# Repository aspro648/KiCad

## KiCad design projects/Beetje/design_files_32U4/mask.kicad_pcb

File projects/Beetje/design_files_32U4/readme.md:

Beetje Blok 32U4

Based on Adafruit's [ItsyBitsy](https://learn.adafruit.com/introducting-itsy-bitsy-32u4) and SparkFun's [Pro Micro](https://www.sparkfun.com/products/12587) 3.3V/8Mhz versions.

Project page on [Hack-A-Day](https://hackaday.io/project/160638-beetje-bloks).

This is the first "dev blok" for this proof-of-concept project.  It is a KiCad mash-up of Adafruit's [ItsyBity](https://learn.adafruit.com/introducting-itsy-bitsy-32u4) and SparkFun's [Pro Micro](https://www.sparkfun.com/products/12587), jammed into Hack-A-Day's [Once Square Inch Scheme](https://hackaday.io/project/7813-the-square-inch-project) ("HADOSIS").

Bill Of Materials
----------------
  
- 1 ea., Perfect Purple PCB from OSH Park, with not so perfect kicad.pcb file.
- 1 ea., U1, ATMEGA32U4-AU, IC MCU 8BIT 32KB FLASH 44TQFP, https://www.digikey.com/short/jb25pc
- 1 ea., U2, IC REG LINEAR 3.3V 150MA SOT23-5, MIC5225-3.3YM5-TR, https://www.digikey.com/short/jb2rq8
- 3 ea,, C1-C3 10uF SMD 0805, https://www.digikey.com/short/j5d39w 
- 1 ea., C4 1uF SMD 0603, https://www.digikey.com/short/j5d397
- 3 ea., D1-D3 0603 SMD LED, https://www.digikey.com/short/j5h3h5
- 2 ea., D4, D5 DIODE SCHOTTKY 20V 1A SOD123FL, MBR120ESFT1G, https://www.digikey.com/short/jnqvz9
- 1 ea., F1 PTC 1206, Bel 0ZCJ0025AF2E, https://www.digikey.com/short/jfcbc8
- 3 ea., R1-R3 1K Ohm 0603 SMD resistor, https://www.digikey.com/short/jfcb32
- 2 ea., R4, R5 Resistor 4.7K SMD 0603, https://www.digikey.com/short/j2d05w
- 2 ea., R6, R7, 22 Ohm 5% 0603 SMD resistor, https://www.digikey.com/short/jfcbtj
- 1 ea., R8 100K ohm 0603 SMD resistor, https://www.digikey.com/short/jnqvjq
- 2 ea., SW1, Sw2 RA Tactile SPST, Pansonic EVQ-P7J01P, https://www.digikey.com/short/jfwprn
- 1 ea., X1 CONN RCPT MICRO USB R/A SMD, Molex 1050170001, https://www.digikey.com/short/jb2205
- 1 ea., Y1 Resonator 8MHZ, CSTNE8M00G55Z000R0, https://www.digikey.com/short/jb22j1

Headers:
--------

- J2, CONN HEADER FEMALE 6POS .1" GOLD, https://www.digikey.com/short/jfcnz3
- J4, CONN HEADER FEMALE 8POS .1" GOLD, https://www.digikey.com/short/jfcnzj
   or
- Stacking Arduino headers like https://www.digikey.com/short/jfcnz3
   or
- 1 ea., 64-pin header(enough for 4.5 boards) Mill-max 311-43-164-41-001000, https://www.digikey.com/short/jnqdm2
   or
- 1 ea., CONN SOCKET SIP 8POS GOLD, Mill-Max 315-47-108-41-001000, https://www.digikey.com/short/jn51q5
- 1 ea., CONN SOCKET SIP 6POS GOLD, Mill-Max 315-47-106-41-001000, https://www.digikey.com/short/jn5188

Revisions
----------------
- Revision 0.1 - Diodes and polyfuse to front.
- Revision 0.2 - I2C pullups, added SW2, enlarge holes for headers.
- Revision 0.3 - Pinout change, rerouted. NOT BACKWARD COMPATIBLE.
- Revision 0.4 - Renumbering, reordering references.

License
----------------
[Attribution-ShareAlike 3.0 United States (CC BY-SA 3.0 US)](https://creativecommons.org/licenses/by-sa/3.0/us/)

You are free to:

- Share — copy and redistribute the material in any medium or format
- Adapt — remix, transform, and build upon the material

Under the following terms:

- Attribution — You must give appropriate credit, provide a link to the license, and indicate if changes were made. You may do so in any reasonable manner, but not in any way that suggests the licensor endorses you or your use.
- ShareAlike — If you remix, transform, or build upon the material, you must distribute your contributions under the same license as the original.

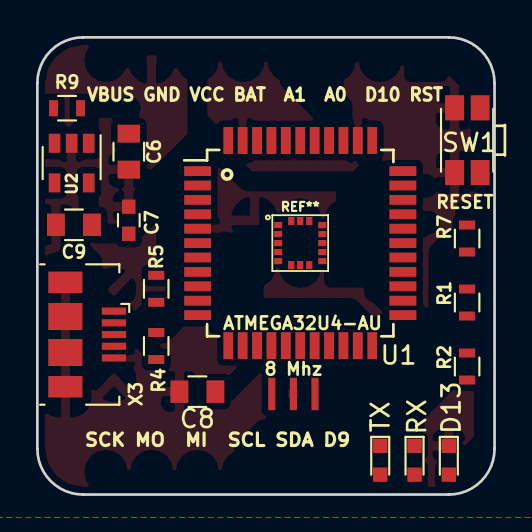
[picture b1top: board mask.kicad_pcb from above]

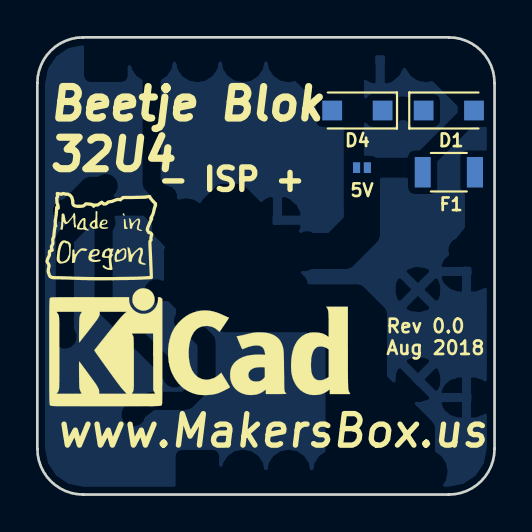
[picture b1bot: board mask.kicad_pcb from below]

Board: 2 copper layers, 25.4 x 25.4 mm, 23 parts (4 on the bottom side), 19 nets, no tracks yet.

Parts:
C6, C8, C9: 10uF; C_0805
C7: 1uF; C_0603
D1, D4: MBR120; D_SOD-123F
D3: TX; LED_0603
D5: RX; LED_0603
D13: D13; LED_0603
F1: Polyfuse; R_1206
JMP1: 5V; Jumper
R1, R2, R7: 180; R_0603
R4, R5: 22; R_0603
R9: 100K; R_0603
SW1: RESET; EVQ-P7A
U1: ATMEGA32U4-AU; TQFP-44_10x10mm_Pitch0.8mm
U2: MIC5225-3.3; SOT-23-5
VAL: MadeInOregonRev25
X3: USB_OTG; USB_Micro-B_Molex-105017-0001
Y1: 8 Mhz; Resonator_SMD_CTSC_1.3mmx3.2mm

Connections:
/D13: R7.2, U1.32
/D+: R4.1, U1.4
/D-: R5.1, U1.3
/RXLED: R2.1, U1.8
/TXLED: R1.1, U1.22
/VHI: C6.1, D1.1, D4.1, R9.2, U2.1
/~RESET: SW1.2, U1.13
GND: C6.2, C7.2, C8.2, C9.2, D13.1, SW1.1, U1.5, U1.15, U1.23, U1.35, U1.43, U2.2, X3.5, X3.6, Y1.2
unnamed: D3.1, R1.2
unnamed: D5.1, R2.2
unnamed: D13.2, R7.1
unnamed: F1.2, X3.1
unnamed: R4.2, X3.3
unnamed: R5.2, X3.2
unnamed: R9.1, U2.3
unnamed: U1.16, Y1.3
unnamed: U1.17, Y1.1
VBUS: D1.2, F1.1, JMP1.2, U1.7
VCC: C7.1, C8.1, C9.1, D3.2, D5.2, JMP1.1, U1.6, U1.14, U1.24, U1.33, U1.34, U1.44, U2.5

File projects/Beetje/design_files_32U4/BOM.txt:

Beetje Blok 32U4 Rev 0.0

Bill Of Materials
----------------
  
- 1 ea., Perfect Purple PCB from OSH Park, with not so perfect layout from [design_files](design_files/) folder.
- U1, ATMEGA32U4-AU, IC MCU 8BIT 32KB FLASH 44TQFP, https://www.digikey.com/short/jb25pc
- U2, IC REG LINEAR 3.3V 150MA SOT23-5, MIC5225-3.3YM5-TR, https://www.digikey.com/short/jb2rq8
- Y1, Resonator 8MHZ, CSTNE8M00G55Z000R0, https://www.digikey.com/short/jb22j1
- D1, D4, DIODE SCHOTTKY 20V 1A SOD123FL, MBR120VLSFT3GOSCT-ND, https://www.digikey.com/short/jb22rn 
- C6, C8, C9, 10uF SMD 0805, https://www.digikey.com/short/j5d39w 
- C7 1uF SMD 0603, https://www.digikey.com/short/j5d397
- X3, CONN RCPT MICRO USB R/A SMD, Molex 1050170001, https://www.digikey.com/short/jb2205
- R4, R5, 22 Ohm 5% 0603 SMD resistor, https://www.digikey.com/short/jfcbtj
- R1, R2, R7, 330 Ohm 0603 SMD resistor, https://www.digikey.com/short/jfcb32
- R9, 100K ohm 0603 SMD resistor, https://www.digikey.com/short/j5d3b3
- D3, D5, D13, 0603 SMD LED, https://www.digikey.com/short/j5h3h5
- F1, PTC 1206, Bel 0ZCJ0025AF2E, https://www.digikey.com/short/jfcbc8
- SW1, RA Tactile SPST, Pansonic EVQ-PA01P, https://www.digikey.com/short/jfc9vq
- J2, CONN HEADER FEMALE 6POS .1" GOLD, https://www.digikey.com/short/jfcnz3
- J4, CONN HEADER FEMALE 8POS .1" GOLD, https://www.digikey.com/short/jfcnzj

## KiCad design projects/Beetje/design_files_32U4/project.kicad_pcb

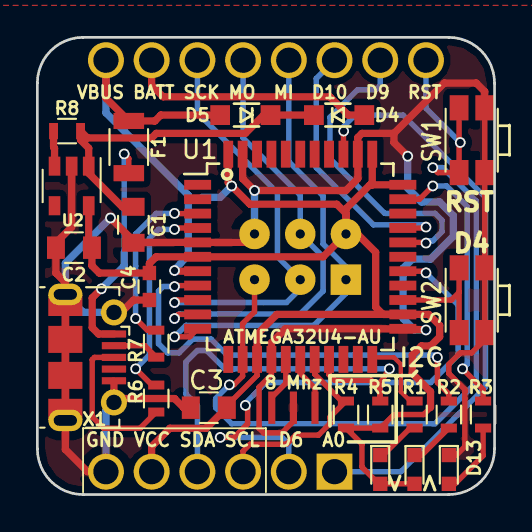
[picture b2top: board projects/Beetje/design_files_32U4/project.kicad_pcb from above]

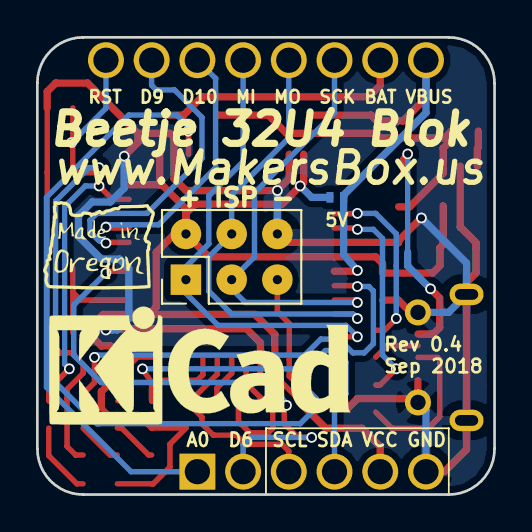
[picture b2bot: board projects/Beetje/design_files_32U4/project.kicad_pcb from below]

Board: 2 copper layers, 25.4 x 25.4 mm, 29 parts (2 on the bottom side), 30 nets.

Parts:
C1, C2, C3: 10uF; C_0805
C4: 1uF; C_0603
CON1: AVR-ISP-6; Pin_Header_Straight_2x03_Pitch2.54mm
D1: TX; LED_0603
D2: RX; LED_0603
D3: D13; LED_0603
D4, D5: MBR120; D_SOD-123F
F1: Polyfuse; R_1206
J2: Beetje Bottom; Beetje_Bottom
J4: Beetje Top; Beetje_Top
JMP1: 5V; Jumper
R1, R2, R3: 1K; R_0603
R4, R5: 4K7; R_0603
R6, R7: 22; R_0603
R8: 100K; R_0603
SW1: RST; EVQ-P7A
SW2: D4; EVQ-P7A
U1: ATMEGA32U4-AU; TQFP-44_10x10mm_Pitch0.8mm
U2: MIC5225-3.3; SOT-23-5
VAL: MadeInOregonRev25
X1: USB_OTG; USB_Micro-B_Molex-105017-0001
Y1: 8 Mhz; Resonator_SMD_CTSC_1.3mmx3.2mm

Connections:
+BATT: D4.2, J4.7
/A0: J2.1, U1.36
/D4: SW2.1, U1.25
/D6: J2.2, U1.27
/D9: J4.2, U1.29
/D10: J4.3, U1.30
/D13: R3.2, U1.32
/D+: R6.1, U1.4
/D-: R7.1, U1.3
/MISO: CON1.1, J4.4, U1.11
/MOSI: CON1.4, J4.5, U1.10
/RXLED: R2.1, U1.8
/SCK: CON1.3, J4.6, U1.9
/SCL: J2.3, R4.1, U1.18
/SDA: J2.4, R5.1, U1.19
/TXLED: R1.1, U1.22
/VHI: C1.1, D4.1, D5.1, R8.2, U2.1
/~RESET: CON1.5, J4.1, SW1.1, U1.13
GND: C1.2, C2.2, C3.2, C4.2, CON1.6, D3.1, J2.6, SW1.2, SW2.2, U1.5, U1.15, U1.23, U1.35, U1.43, U2.2, X1.5, X1.6, Y1.2
unnamed: D1.1, R1.2
unnamed: D2.1, R2.2
unnamed: D3.2, R3.1
unnamed: F1.2, X1.1
unnamed: R6.2, X1.3
unnamed: R7.2, X1.2
unnamed: R8.1, U2.3
unnamed: U1.16, Y1.3
unnamed: U1.17, Y1.1
VBUS: D5.2, F1.1, J4.8, JMP1.2, U1.7
VCC: C2.1, C3.1, C4.1, CON1.2, D1.2, D2.2, J2.5, JMP1.1, R4.2, R5.2, U1.6, U1.14, U1.24, U1.33, U1.34, U1.44, U2.5

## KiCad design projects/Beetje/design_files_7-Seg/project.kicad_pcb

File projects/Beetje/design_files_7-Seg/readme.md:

Beetje Blok 7-SEG Rev 0.0

Project website: https://hackaday.io/project/160638-beetje-bloks

Based on Adafruit's [LED Backpack]{https://learn.adafruit.com/adafruit-led-backpack/downloads}. 

Bill Of Materials
----------------
  
- 1 ea., Perfect Purple PCB from OSH Park, with not so perfect layout from [design_files](design_files/) folder.
- 1 ea., IC1 Holtek HT16K33, https://lcsc.com/product-detail/LED-Drivers_HT16K33_C87502.html
- 1 ea., U1 7-segment CC LED
- 1 ea., C1 CAP CER 10UF 50V X7R, https://www.digikey.com/short/j5d39w 
- 1 ea., D1 DIODE SCHOTTKY 20V 1A SOD123L, https://www.digikey.com/short/j2wzf5
- 2 ea., R1, R2 Resistor 10K 0805 SMD, https://www.digikey.com/short/j2d0w4
- 3 ea., R3, R4, R5 Resistor 47K 0805 SMD, https://www.digikey.com/short/j2d00m 
- 1 ea., CONN HEADER .100" SNGL STR 40POS, https://www.digikey.com/short/jfcn42
- 1 ea., SW1 RA Tactile SPST, Pansonic EVQ-P7J01P, https://www.digikey.com/short/jfwprn

try https://lcsc.com/product-detail/Led-Segment-Display_0-28-Digitron-red-RED_C109199.html

License
----------------
[Attribution-ShareAlike 3.0 United States (CC BY-SA 3.0 US)](https://creativecommons.org/licenses/by-sa/3.0/us/)

You are free to:

- Share — copy and redistribute the material in any medium or format
- Adapt — remix, transform, and build upon the material

Under the following terms:

- Attribution — You must give appropriate credit, provide a link to the license, and indicate if changes were made. You may do so in any reasonable manner, but not in any way that suggests the licensor endorses you or your use.
- ShareAlike — If you remix, transform, or build upon the material, you must distribute your contributions under the same license as the original.

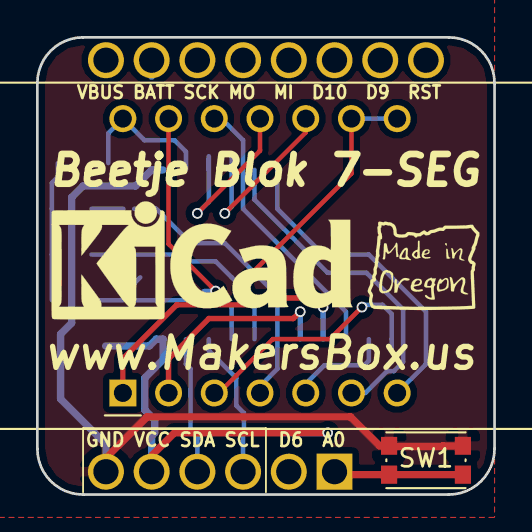
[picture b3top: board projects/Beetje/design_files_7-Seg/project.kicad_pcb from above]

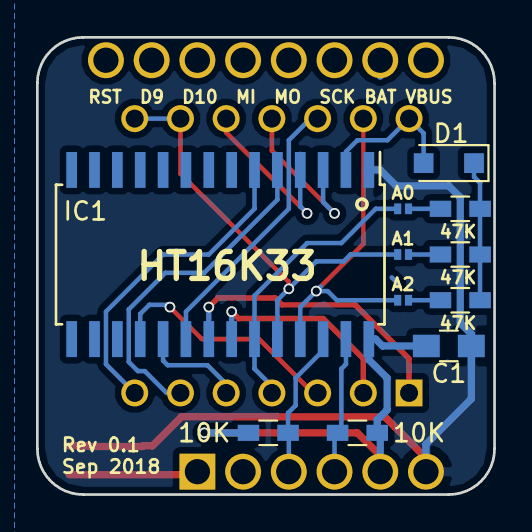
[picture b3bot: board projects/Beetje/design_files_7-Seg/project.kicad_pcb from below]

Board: 2 copper layers, 25.4 x 25.4 mm, 16 parts (12 on the bottom side), 22 nets.

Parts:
A0, A1, A2: JMP; Jumper
C1: 10uF; C_0805_HandSoldering
D1: D; D_SOD-123F
IC1: HT16K33; SOIC-28W_7.5x17.9mm_Pitch1.27mm
J2: Beetje_Bottom
J4: Beetje_Top
R1, R2: 10K; R_0603_HandSoldering
R3, R4, R5: 47K; R_0603_HandSoldering
SW1: SW_Push; SW_SPST_KMR2
U3: KW4-56xxx; CA56-12CGKWA
VAL: MadeInOregonRev25

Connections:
/A0: A0.2, IC1.23, U3.4
/A1: A1.2, IC1.24, U3.8, U3.9
/A2: A2.2, IC1.25, U3.13
/An0: J2.1, SW1.1
/SCL: IC1.26, J2.3, R2.1
/SDA: IC1.27, J2.4, R1.1
GND: C1.2, IC1.1, J2.6, SW1.2
unnamed: A0.1, R3.1
unnamed: A1.1, R4.1
unnamed: A2.1, R5.1
unnamed: D1.1, R3.2, R4.2, R5.2
unnamed: D1.2, IC1.2, U3.14
unnamed: IC1.3, U3.11
unnamed: IC1.4, U3.10
unnamed: IC1.5, U3.6
unnamed: IC1.6, U3.7
unnamed: IC1.18, U3.3
unnamed: IC1.19, U3.5
unnamed: IC1.20, U3.12
unnamed: IC1.21, U3.1
unnamed: IC1.22, U3.2
VCC: C1.1, IC1.28, J2.5, R1.2, R2.2

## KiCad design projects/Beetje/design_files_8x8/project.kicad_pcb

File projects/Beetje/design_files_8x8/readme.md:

Beetje Blok 7-SEG Rev 0.0

Project website: https://hackaday.io/project/160638-beetje-bloks

Based on Adafruit's [LED Backpack]{https://learn.adafruit.com/adafruit-led-backpack/downloads}. 

Bill Of Materials
----------------
  
- 1 ea., Perfect Purple PCB from OSH Park, with not so perfect layout from [design_files](design_files/) folder.
- 1 ea., IC1 Holtek HT16K33
- 1 ea., U1 7-segment CC LED
- 1 ea., C1 CAP CER 10UF 50V X7R, https://www.digikey.com/short/j5d39w 
- 2 ea., R1, R2 Resistor 10K 0805 SMD, https://www.digikey.com/short/j2d0w4
- 3 ea., R3, R4, R5 Resistor 47K 0805 SMD, https://www.digikey.com/short/j2d00m 
- 1 ea., CONN HEADER .100" SNGL STR 40POS, https://www.digikey.com/short/jfcn42
- 1 ea., SW1 RA Tactile SPST, Pansonic EVQ-P7J01P, https://www.digikey.com/short/jfwprn

License
----------------
[Attribution-ShareAlike 3.0 United States (CC BY-SA 3.0 US)](https://creativecommons.org/licenses/by-sa/3.0/us/)

You are free to:

- Share — copy and redistribute the material in any medium or format
- Adapt — remix, transform, and build upon the material

Under the following terms:

- Attribution — You must give appropriate credit, provide a link to the license, and indicate if changes were made. You may do so in any reasonable manner, but not in any way that suggests the licensor endorses you or your use.
- ShareAlike — If you remix, transform, or build upon the material, you must distribute your contributions under the same license as the original.

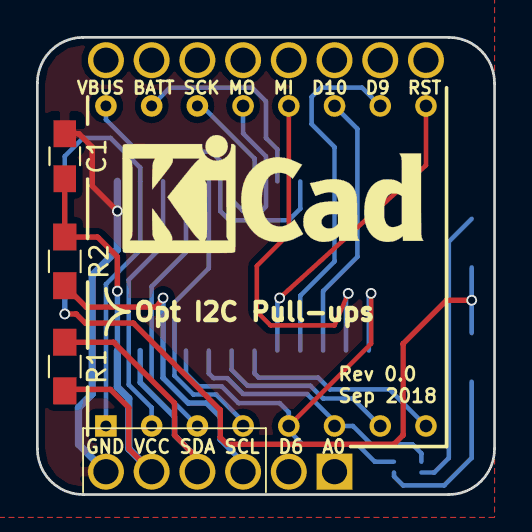
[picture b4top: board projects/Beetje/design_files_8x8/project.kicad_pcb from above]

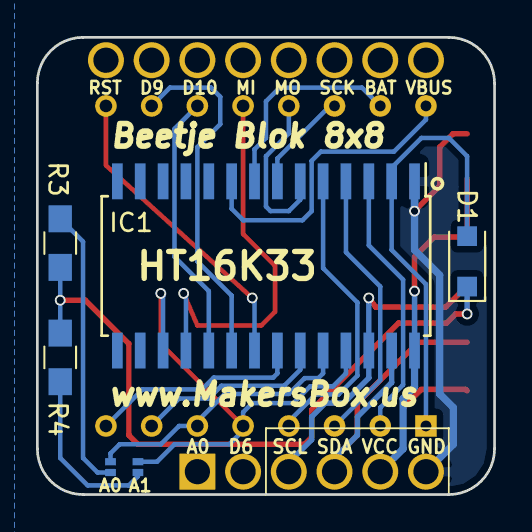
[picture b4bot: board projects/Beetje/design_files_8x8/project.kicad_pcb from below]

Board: 2 copper layers, 25.4 x 25.4 mm, 13 parts (6 on the bottom side), 23 nets.

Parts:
A0, A1: JMP; Jumper
C1: 10uF; C_0805_HandSoldering
D1: D; D_SOD-123F
IC1: HT16K33; SOIC-28W_7.5x17.9mm_Pitch1.27mm
J1, J3: CONN_01X08; Pin_Header_Straight_1x08_Pitch2.54mm
J2: Beetje_Bottom
J4: Beetje_Top
R1, R2, R3, R4: 10K; R_0805_HandSoldering

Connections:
/P1: D1.2, IC1.2, J3.1
/P2: IC1.3, J3.2
/P3: IC1.4, J3.3
/P4: IC1.5, J3.4
/P5: A1.2, IC1.17, IC1.25, J3.5
/P6: A0.2, IC1.24, J3.6
/P7: IC1.23, J3.7
/P8: IC1.22, J3.8
/P9: IC1.9, J1.1
/P10: IC1.8, J1.2
/P11: IC1.7, J1.3
/P12: IC1.6, J1.4
/P13: IC1.18, J1.5
/P14: IC1.19, J1.6
/P15: IC1.20, J1.7
/P16: IC1.21, J1.8
/SCL: IC1.26, J2.3, R2.1
/SDA: IC1.27, J2.4, R1.1
GND: C1.2, IC1.1, J2.6
unnamed: A0.1, R3.1
unnamed: A1.1, R4.1
unnamed: D1.1, R3.2, R4.2
VCC: C1.1, IC1.28, J2.5, R1.2, R2.2

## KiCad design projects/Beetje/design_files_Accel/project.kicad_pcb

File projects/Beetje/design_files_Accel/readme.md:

Beetje Blok Accel

Project website: https://hackaday.io/project/160638-beetje-bloks

Bill Of Materials
----------------
  
- 1 ea., Perfect Purple PCB from OSH Park, with not so perfect layout from [project.kicad_pcb](project.kicad_pcb) file.
- 1 ea., U1 ACCEL 2-16G I2C/SPI 16LGA, STM LIS331DLHTR, https://www.digikey.com/short/zzdzr7
- 1 ea., C1 10uF CAP SMD 0805, https://www.digikey.com/short/jnwj88
- 1 ea., C2 0.1uF CAP SMD 0805, https://www.digikey.com/short/j58qjp
- 1 ea., R1 10K OHM SMD 0805, https://www.digikey.com/short/j2d0w4 
- 2 ea., R2, R3 4K7 OHM SMD 0805, https://www.digikey.com/short/j2d0wd

Revisions
------------------

0.1 Pinout to Rev 0.3, 0805 Footprints

License
----------------
[Attribution-ShareAlike 3.0 United States (CC BY-SA 3.0 US)](https://creativecommons.org/licenses/by-sa/3.0/us/)

You are free to:

- Share — copy and redistribute the material in any medium or format
- Adapt — remix, transform, and build upon the material

Under the following terms:

- Attribution — You must give appropriate credit, provide a link to the license, and indicate if changes were made. You may do so in any reasonable manner, but not in any way that suggests the licensor endorses you or your use.
- ShareAlike — If you remix, transform, or build upon the material, you must distribute your contributions under the same license as the original.

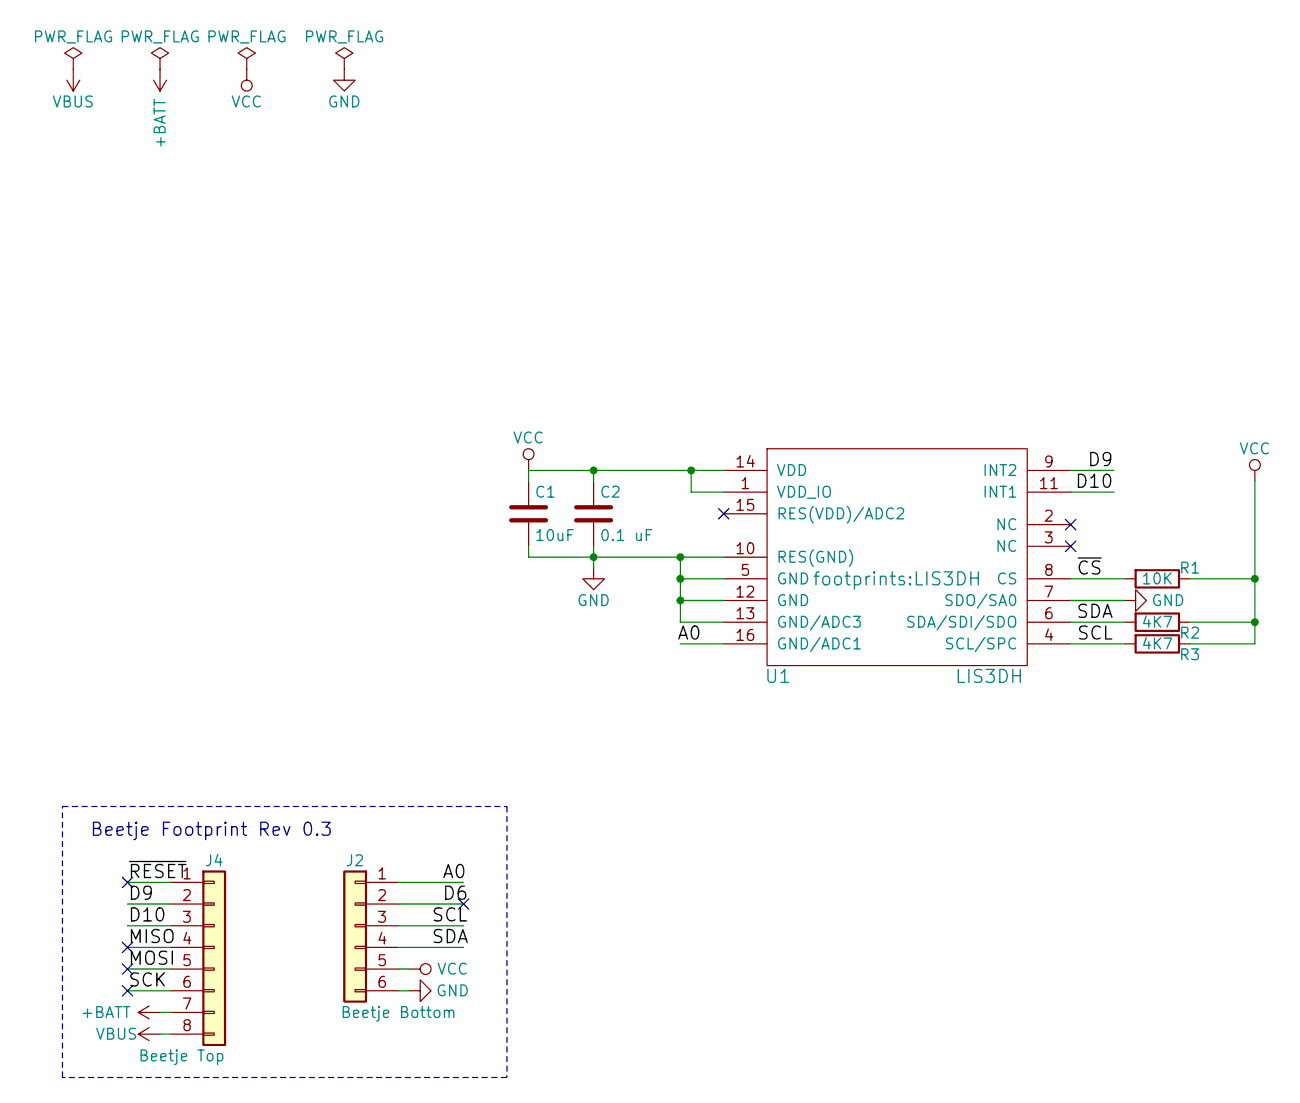
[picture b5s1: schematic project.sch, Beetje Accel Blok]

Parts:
C1: 10uF; C_0805
C2: 0.1 uF; C_0603
J2: Beetje Bottom; Beetje_Bottom
J4: Beetje Top; Beetje_Top
R1: 10K; R_0603
R2, R3: 4K7; R_0603
U1: LIS3DH

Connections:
+BATT: J4.7
/A0: J2.1, U1.16 (GND/ADC1)
/D6: J2.2
/D9: J4.2, U1.9 (INT2)
/D10: J4.3, U1.11 (INT1)
/MISO: J4.4
/MOSI: J4.5
/SCK: J4.6
/SCL: J2.3, R3.2, U1.4 (SCL/SPC)
/SDA: J2.4, R2.2, U1.6 (SDA/SDI/SDO)
/~CS: R1.2, U1.8 (CS)
/~RESET: J4.1
GND: C1.2, C2.2, J2.6, U1.5 (GND), U1.7 (SDO/SA0), U1.10 (RES(GND)), U1.12 (GND), U1.13 (GND/ADC3)
VBUS: J4.8
VCC: C1.1, C2.1, J2.5, R1.1, R2.1, R3.1, U1.1 (VDD_IO), U1.14 (VDD)

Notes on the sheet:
Beetje Footprint Rev 0.3

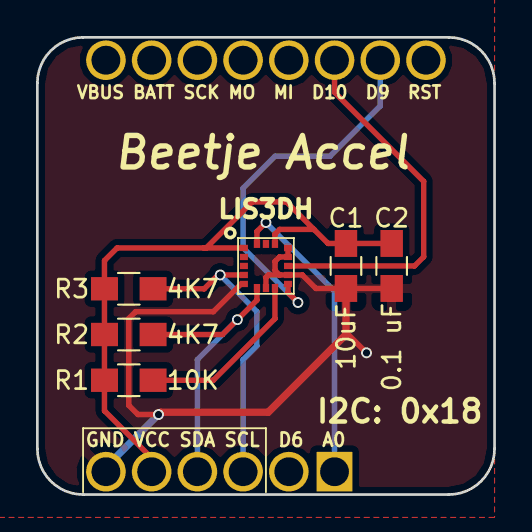
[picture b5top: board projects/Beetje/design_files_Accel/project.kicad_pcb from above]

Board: 2 copper layers, 25.4 x 25.4 mm, 9 parts (0 on the bottom side), 8 nets.

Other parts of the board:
VAL: MadeInOregonRev25

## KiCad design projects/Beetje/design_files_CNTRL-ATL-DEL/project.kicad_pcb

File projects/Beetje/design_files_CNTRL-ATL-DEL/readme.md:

Beetje Blok Template

Project website: https://hackaday.io/project/160638-beetje-bloks
Cherry Key footprint: https://github.com/BathroomEpiphanies/KiCAD-Keyboard-Tutorial

Bill Of Materials
----------------
  
- 1 ea., Perfect Purple PCB from OSH Park, with not so perfect layout from [project.kicad_pcb](project.kicad_pcb) file.
- 1 ea.,  https://www.banggood.com/10-Pcs-Cherry-Red-3-Pin-MX-RGB-Series-Mechanical-Switch-Keyboard-Replacement-p-1114348.html
- 1 ea., https://www.banggood.com/R4-ESC-PBT-Red-Blank-Keycaps-Key-Caps-for-Mechanical-Gaming-Keyboard-p-1173201.html
- 1 ea., 64-pin header(enough for 4.5 boards) Mill-max 311-43-164-41-001000, https://www.digikey.com/short/jnqdm2

Firmware
-----------------
Since the 32U4 chip can act as a USB HID, it can send keystrokes (or mouse movements) to an attached computer.
Using the Arduino example sketch ([File]->[Examples]->[USB]->[Keyboard]->[KeyboardLogout]), we can send appropriate keystrokes to lock or unlock the computer.  Of course, putting your password in there is not a good idea, but locking and getting to the login screen with a single button press is.  Modified sketch (originally written by the Tom Igo!) is located in the [/firmware](/firmware)folder.

License
----------------
[Attribution-ShareAlike 3.0 United States (CC BY-SA 3.0 US)](https://creativecommons.org/licenses/by-sa/3.0/us/)

You are free to:

- Share — copy and redistribute the material in any medium or format
- Adapt — remix, transform, and build upon the material

Under the following terms:

- Attribution — You must give appropriate credit, provide a link to the license, and indicate if changes were made. You may do so in any reasonable manner, but not in any way that suggests the licensor endorses you or your use.
- ShareAlike — If you remix, transform, or build upon the material, you must distribute your contributions under the same license as the original.

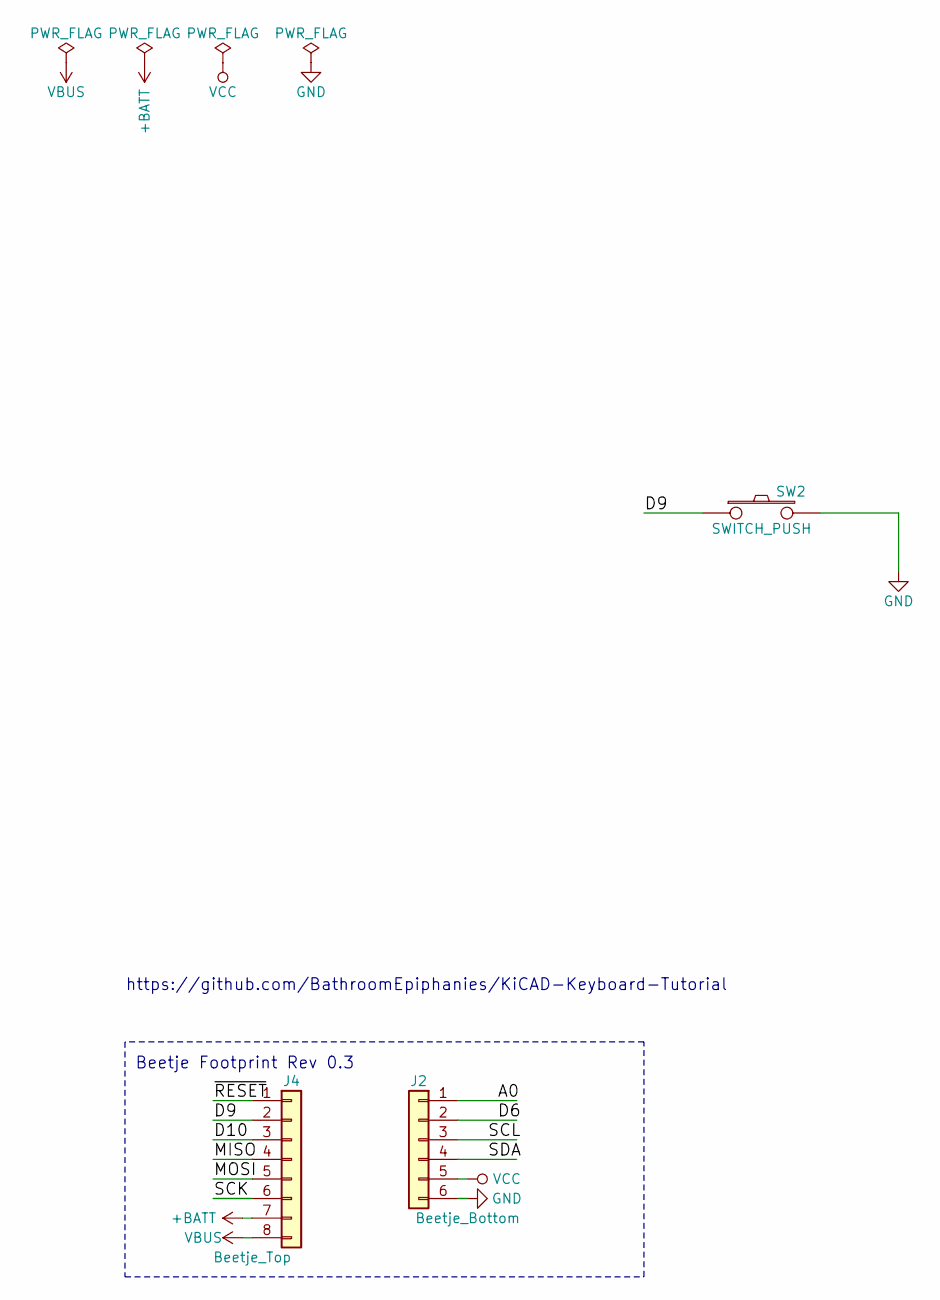
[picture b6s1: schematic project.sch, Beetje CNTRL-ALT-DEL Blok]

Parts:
J2: Beetje_Bottom
J4: Beetje_Top
SW2: SWITCH_PUSH; CHERRY_PCB_100H

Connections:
+BATT: J4.7
/A0: J2.1
/D6: J2.2
/D9: J4.2, SW2.1
/D10: J4.3
/MISO: J4.4
/MOSI: J4.5
/SCK: J4.6
/SCL: J2.3
/SDA: J2.4
/~RESET: J4.1
GND: J2.6, SW2.2
VBUS: J4.8
VCC: J2.5

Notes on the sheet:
Beetje Footprint Rev 0.3
https://github.com/BathroomEpiphanies/KiCAD-Keyboard-Tutorial

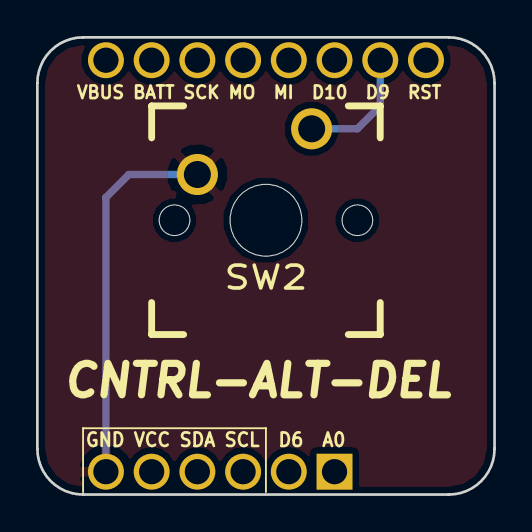
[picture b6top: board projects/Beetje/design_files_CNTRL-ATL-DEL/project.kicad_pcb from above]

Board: 2 copper layers, 25.4 x 25.4 mm, 4 parts (0 on the bottom side), 2 nets.

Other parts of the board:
VAL: MadeInOregonRev25
